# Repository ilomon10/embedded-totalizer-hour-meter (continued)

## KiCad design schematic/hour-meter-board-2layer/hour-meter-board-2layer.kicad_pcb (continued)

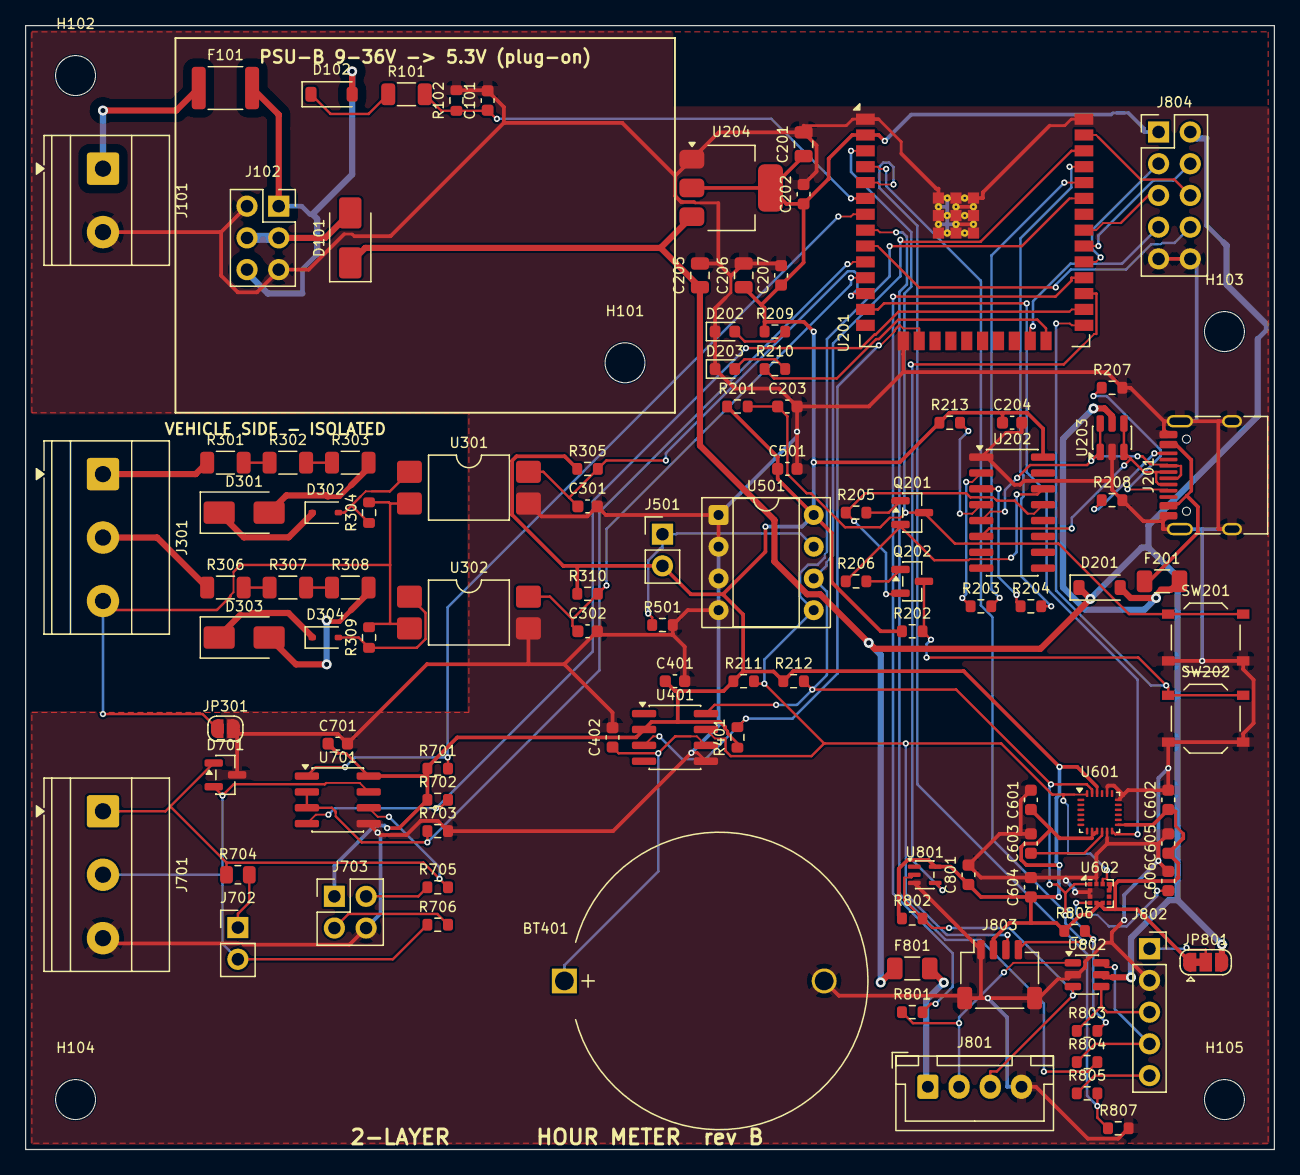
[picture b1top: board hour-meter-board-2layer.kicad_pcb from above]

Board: 2 copper layers, 100.0 x 90.0 mm, 111 parts (0 on the bottom side), 77 nets.

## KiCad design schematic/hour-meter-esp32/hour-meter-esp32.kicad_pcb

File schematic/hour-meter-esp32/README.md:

# Hour Meter ESP32: carrier PCB (rev A)

A 130 × 100 mm, 2-layer, through-hole carrier board. The ESP32 DevKit and the sensor modules plug into sockets, the 817 module and the LM2596 module mount on it, and vehicle wires go to screw terminals.

| | |
|---|---|
| Schematic | `hour-meter-esp32.kicad_sch` (PDF: `hour-meter-esp32.pdf`, picture: `hour-meter-esp32.png`) |
| PCB | `hour-meter-esp32.kicad_pcb` (pictures: `hour-meter-esp32-pcb.png`, `hour-meter-esp32-3d.png`) |
| Ready to order | `production/hour-meter-esp32-gerbers-JLCPCB.zip` (Gerbers + drill), `production/hour-meter-esp32-bom.csv` |
| Custom parts | `hour-meter-modules.kicad_sym` (symbols), `hour-meter-modules.pretty/` (footprints) |
| Wiring notes | [`esp32/docs/WIRING.md`](../../esp32/docs/WIRING.md) |

**Checks at release:** ERC 0 errors and 0 warnings; DRC 0 errors, 0 warnings, 0 unconnected, 0 schematic mismatches; Konnect JLCPCB pre-flight READY.

## ⚠ Measure before you order

The module footprints use **typical clone dimensions**. Check them against your parts with calipers. Open `hour-meter-modules.pretty/` in the KiCad footprint editor, or edit the numbers in `tools-gen-footprints.py`.

| Part | Assumed | Check |
|---|---|---|
| ESP32 DevKit V1 30-pin | 2 × 15 pins, **rows 25.4 mm apart** | Some 30-pin boards use 22.86 mm. Measure pin-row to pin-row |
| 817 module | 38 × 29 mm board, 4 × M3 holes 3 mm from the corners | Hole positions; it mounts on standoffs and is wired from its screw terminals to the `IN` / `OUT` pads |
| LM2596 module | 43 × 21 mm, pads 38.1 mm × 15.24 mm apart | Pad positions vary a lot between clones |
| GY-9250 (MPU9250) | 10 pins in a row, board lies flat toward +X | Lies flat with its chip facing up, so the firmware's "z up" holds |
| DS3231 ZS-042 | 6-pin socket, module stands upright | |
| AT24C256 | 5-pin socket (VCC GND SCL SDA WP) | Many boards have a 4-pin header plus a WP jumper. Leave pin 5 empty and set WP with the jumper |
| F1 | MF-R050 (60 V) on the MF-RHT050 footprint | Lead spacing is about 5.1 mm on both; check your part |

## Ordering (JLCPCB)

Upload `production/hour-meter-esp32-gerbers-JLCPCB.zip`. Settings: 2 layers, 1.6 mm, HASL (lead-free), 1 oz copper, any colour. No assembly is needed: all parts are through-hole and hand-soldered (BOM in `production/`).

## Assembly order

1. Low parts first: D1–D4, R4–R7, C1–C2, F1.
2. Then C3 (mind the polarity), the screw terminals J1/J2/J4, header J3, and the female sockets.
3. **Power test without modules:** fit M5 (LM2596), apply 12/24 V to J4, and **turn the trimmer until OUT+ reads 5.0 V**. Only then fit the ESP32.
4. Mount the 817 module on standoffs, **remove both G jumpers**, and wire IN1/G/IN2/G and V1/V2/G/G to the pads.
5. Plug in the ESP32 (antenna toward the board edge, USB toward the "USB" mark), DS3231, AT24C256 and MPU9250.

## Design notes

- **Isolation:** the vehicle-input area (J1, J2, D1/D2, R4/R6, 817 inputs) has no ground pour, and its nets use 0.8 mm clearance (`Vehicle` netclass). Ground pours cover the rest of the board on both layers.
- **Power:** 12/24 V → F1 PTC → D3 (reverse polarity) → D4 TVS + C3 → LM2596 → +5 V → ESP32 VIN. Power traces are 0.8 mm (`Power` netclass).
- **Antenna:** the area under the ESP32 antenna is a copper keep-out.
- **Grounds:** if J4's ground and the vehicle ground are the same chassis (usual), the 817 module still protects the GPIOs from spikes, but the grounds are no longer isolated. See WIRING.md.

## Re-generating after a change

The board is produced by scripts, so a change is three commands:

```bash
python3 tools-gen-footprints.py      # 1. footprints (after editing dimensions)
python3 tools-build-pcb.py place     # 2. netlist -> footprints -> placement (edit PLACEMENT for positions)
python3 tools-route-pcb.py           # 3. keep-outs -> Freerouting -> GND pours
```

Then run DRC in KiCad (or `kicad-cli pcb drc`) and re-export the Gerbers. Freerouting is not deterministic, so a re-run gives slightly different traces.

To adjust by hand instead, open `hour-meter-esp32.kicad_pro` in KiCad, move parts, and re-route with the interactive router. The scripts are only needed for a full regeneration.

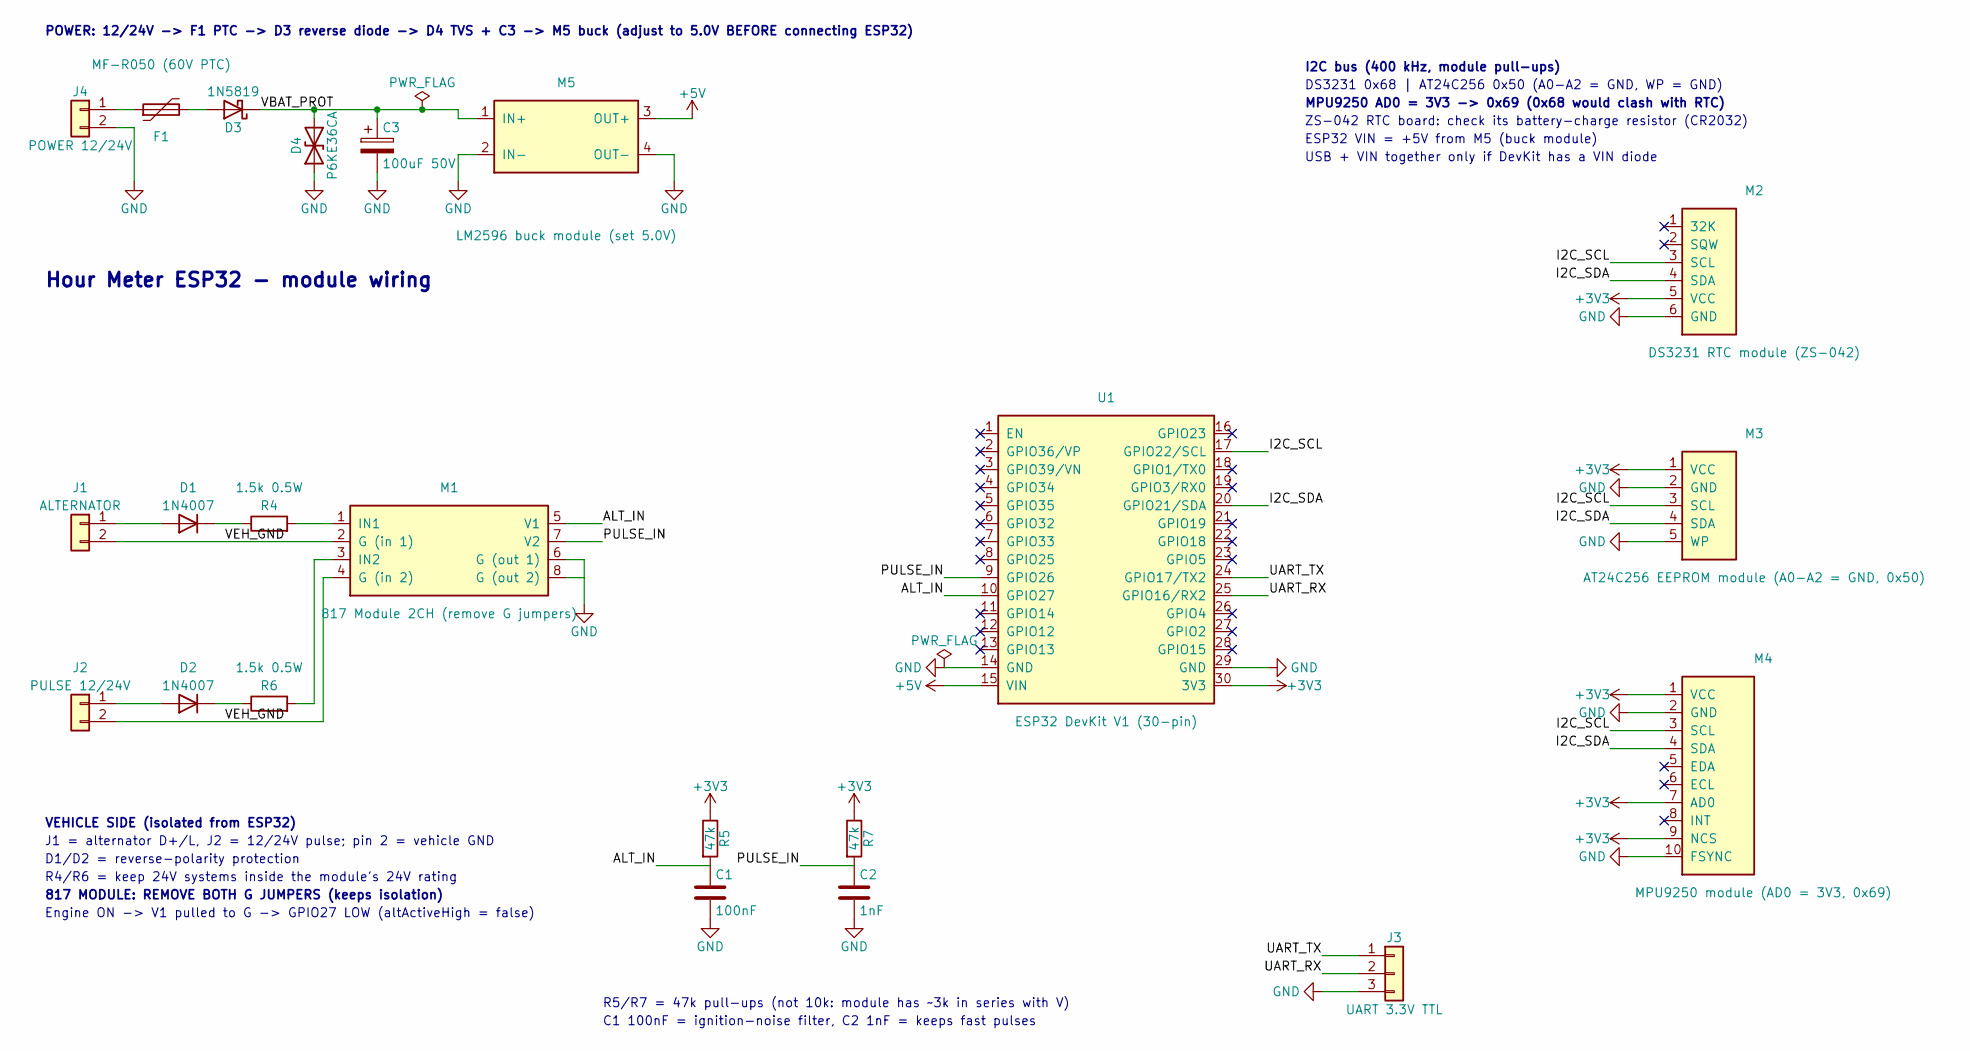
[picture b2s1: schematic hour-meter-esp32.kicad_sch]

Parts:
C1: 100nF; C_Disc_D5.0mm_W2.5mm_P5.00mm
C2: 1nF; C_Disc_D5.0mm_W2.5mm_P5.00mm
C3: 100uF 50V; CP_Radial_D8.0mm_P3.50mm
D1, D2: 1N4007; D_DO-41_SOD81_P10.16mm_Horizontal
D3: 1N5819; D_DO-41_SOD81_P10.16mm_Horizontal
D4: P6KE36CA; D_DO-15_P10.16mm_Horizontal
F1: MF-R050 (60V PTC); Fuse_Bourns_MF-RHT050
J1: ALTERNATOR; TerminalBlock_Phoenix_MKDS-1,5-2-5.08_1x02_P5.08mm_Horizont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
J2: PULSE 12/24V; TerminalBlock_Phoenix_MKDS-1,5-2-5.08_1x02_P5.08mm_Horizont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
J3: UART 3.3V TTL; PinHeader_1x03_P2.54mm_Vertical
J4: POWER 12/24V; TerminalBlock_Phoenix_MKDS-1,5-2-5.08_1x02_P5.08mm_Horizont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
M1: 817 Module 2CH (remove G jumpers); Module_PC817_2CH_Wired
M2: DS3231 RTC module (ZS-042); Module_DS3231_ZS042_Socket
M3: AT24C256 EEPROM module (A0-A2 = GND, 0x50); Module_AT24C256_Socket
M4: MPU9250 module (AD0 = 3V3, 0x69); Module_MPU9250_GY9250_Socket
M5: LM2596 buck module (set 5.0V); Module_LM2596_Buck
R4, R6: 1.5k 0.5W; R_Axial_DIN0309_L9.0mm_D3.2mm_P12.70mm_Horizontal
R5, R7: 47k; R_Axial_DIN0207_L6.3mm_D2.5mm_P10.16mm_Horizontal
U1: ESP32 DevKit V1 (30-pin); ESP32_DevKit_V1_30pin_Socket

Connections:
+3V3: M2.5 (VCC), M3.1 (VCC), M4.1 (VCC), M4.7 (AD0), M4.9 (NCS), R5.1, R7.1, U1.30 (3V3)
+5V: M5.3 (OUT+), U1.15 (VIN)
/ALT_IN: C1.1, M1.5 (V1), R5.2, U1.10 (GPIO27)
/I2C_SCL: M2.3 (SCL), M3.3 (SCL), M4.3 (SCL), U1.17 (GPIO22/SCL)
/I2C_SDA: M2.4 (SDA), M3.4 (SDA), M4.4 (SDA), U1.20 (GPIO21/SDA)
/PULSE_IN: C2.1, M1.7 (V2), R7.2, U1.9 (GPIO26)
/UART_RX: J3.2, U1.25 (GPIO16/RX2)
/UART_TX: J3.1, U1.24 (GPIO17/TX2)
/VBAT_PROT: C3.1, D3.1 (K), D4.2 (A2), M5.1 (IN+)
/VEH_GND: J1.2, J2.2, M1.2 (G (in 1)), M1.4 (G (in 2))
GND: C1.2, C2.2, C3.2, D4.1 (A1), J3.3, J4.2, M1.6 (G (out 1)), M1.8 (G (out 2)), M2.6 (GND), M3.2 (GND), M3.5 (WP), M4.2 (GND), M4.10 (FSYNC), M5.2 (IN-), M5.4 (OUT-), U1.14 (GND), U1.29 (GND)
unnamed: D1.2 (A), J1.1
unnamed: D1.1 (K), R4.1
unnamed: D2.2 (A), J2.1
unnamed: D2.1 (K), R6.1
unnamed: D3.2 (A), F1.2
unnamed: F1.1, J4.1
unnamed: M1.1 (IN1), R4.2
unnamed: M1.3 (IN2), R6.2

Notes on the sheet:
Hour Meter ESP32 - module wiring
VEHICLE SIDE (isolated from ESP32)
J1 = alternator D+/L, J2 = 12/24V pulse; pin 2 = vehicle GND
D1/D2 = reverse-polarity protection
R4/R6 = keep 24V systems inside the module's 24V rating
817 MODULE: REMOVE BOTH G JUMPERS (keeps isolation)
Engine ON -> V1 pulled to G -> GPIO27 LOW (altActiveHigh = false)
R5/R7 = 47k pull-ups (not 10k: module has ~3k in series with V)
C1 100nF = ignition-noise filter, C2 1nF = keeps fast pulses
I2C bus (400 kHz, module pull-ups)
DS3231 0x68 | AT24C256 0x50 (A0-A2 = GND, WP = GND)
MPU9250 AD0 = 3V3 -> 0x69 (0x68 would clash with RTC)
ZS-042 RTC board: check its battery-charge resistor (CR2032)
POWER: 12/24V -> F1 PTC -> D3 reverse diode -> D4 TVS + C3 -> M5 buck (adjust to 5.0V BEFORE connecting ESP32)
ESP32 VIN = +5V from M5 (buck module)
USB + VIN together only if DevKit has a VIN diode

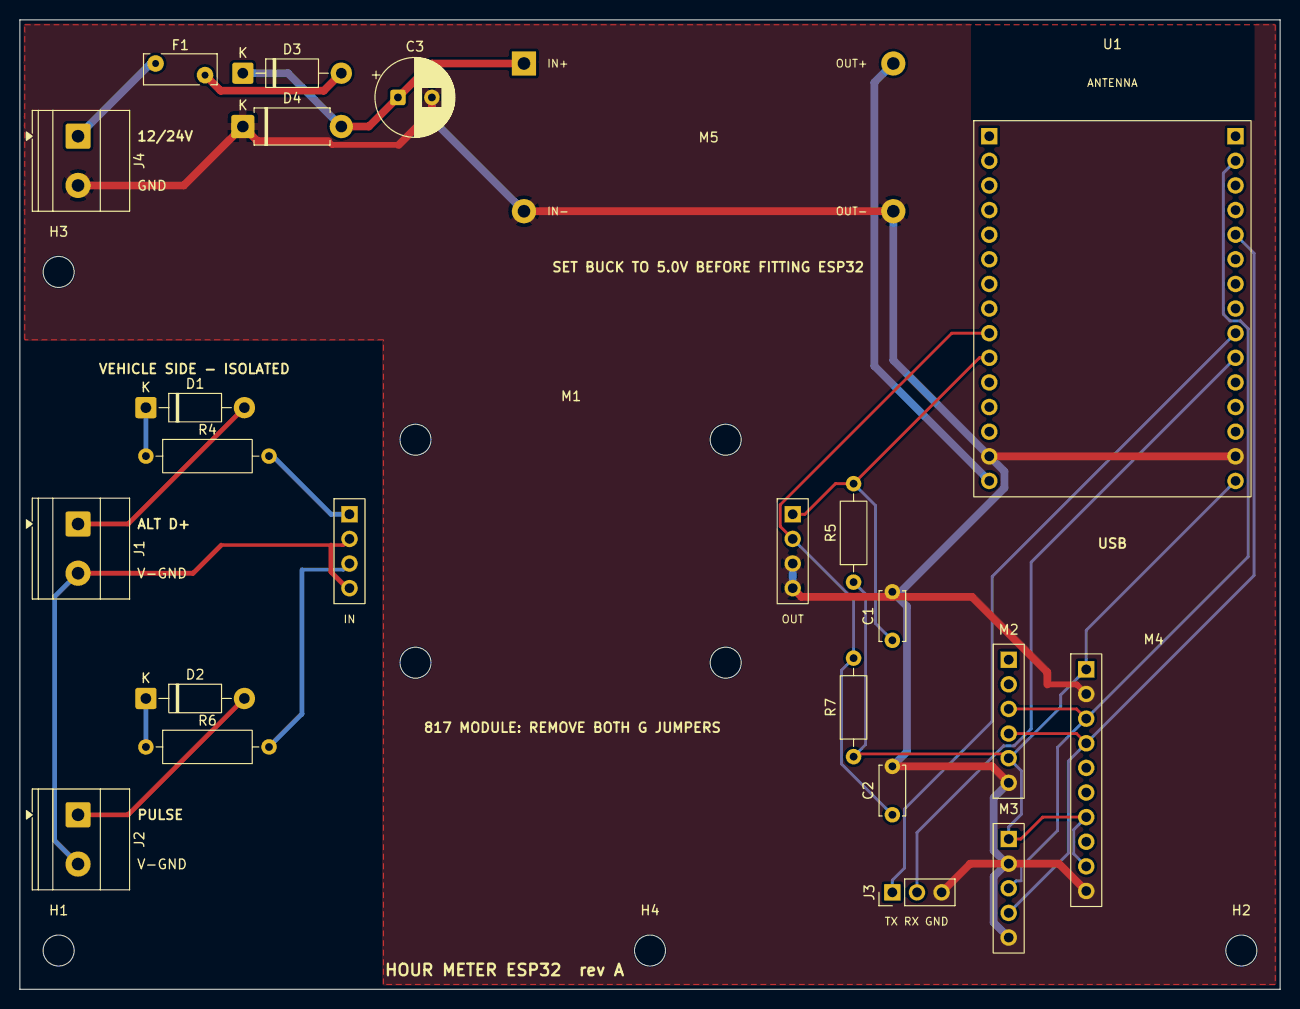
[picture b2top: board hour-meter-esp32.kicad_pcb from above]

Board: 2 copper layers, 130.0 x 100.0 mm, 26 parts (0 on the bottom side), 19 nets.

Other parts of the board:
H1, H2, H3, H4: MountingHole_3.2mm_M3

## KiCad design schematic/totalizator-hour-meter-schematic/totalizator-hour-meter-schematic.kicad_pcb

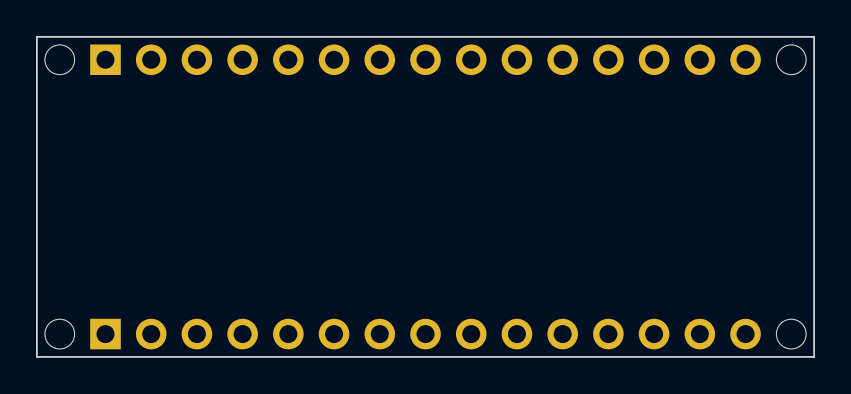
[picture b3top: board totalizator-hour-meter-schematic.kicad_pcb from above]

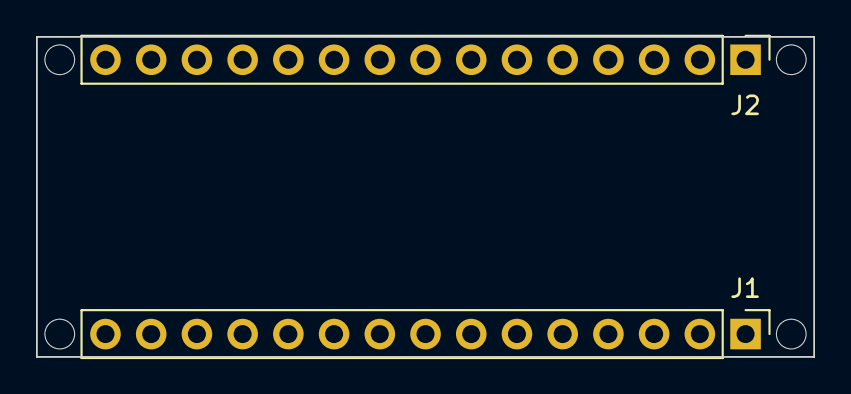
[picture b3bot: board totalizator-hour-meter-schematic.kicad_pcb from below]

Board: 2 copper layers, 43.2 x 17.8 mm, 6 parts (2 on the bottom side), 2 nets, no tracks yet.

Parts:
J1: Analog; PinHeader_1x15_P2.54mm_Vertical
J2: Digital; PinHeader_1x15_P2.54mm_Vertical
MH1, MH2, MH3, MH4: MountingHole_65mil

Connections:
/~RESET: J1.13, J2.13
GND: J1.14, J2.12
